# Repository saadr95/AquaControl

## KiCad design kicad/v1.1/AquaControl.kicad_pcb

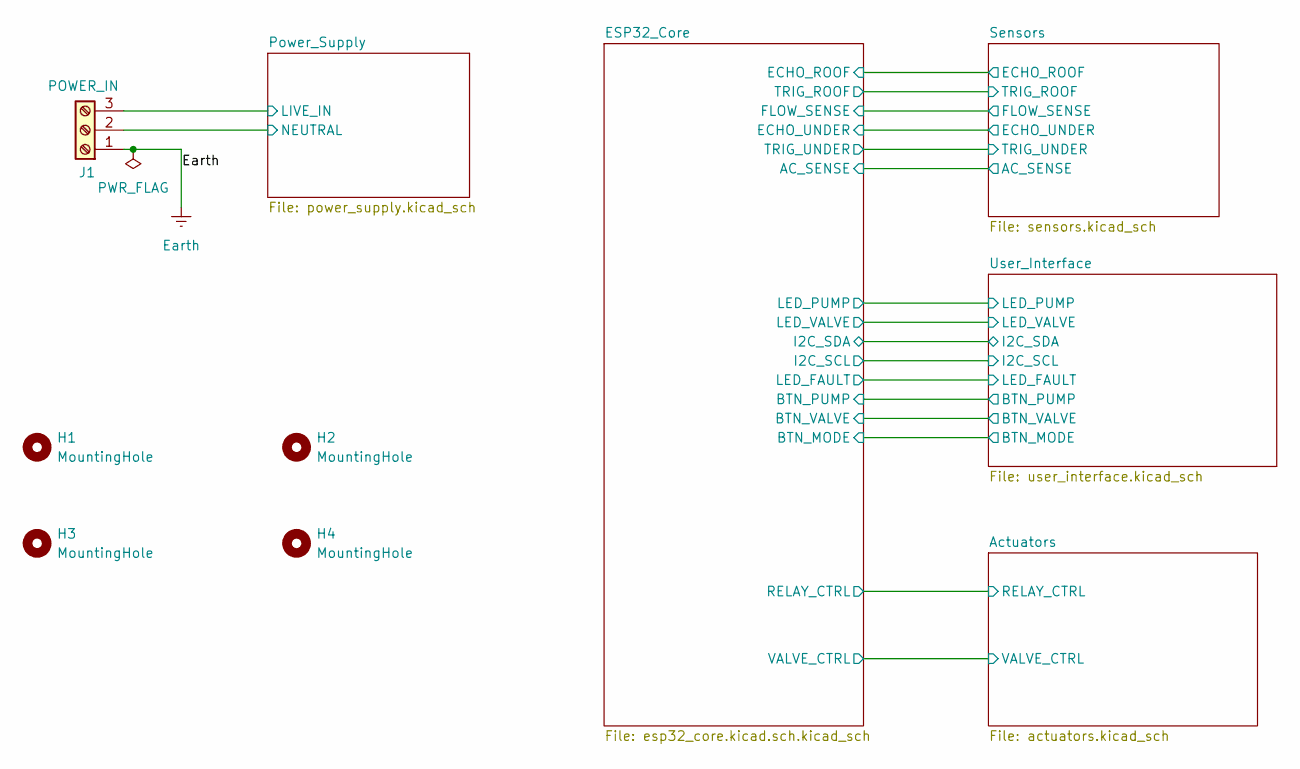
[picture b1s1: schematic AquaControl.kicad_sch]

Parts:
H1, H2, H3, H4: MountingHole; MountingHole_3.2mm_M3
J1: POWER_IN; TerminalBlock_Phoenix_MKDS-1,5-3_1x03_P5.00mm_Horizontal; LCSC C8427

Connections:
/Power_Supply/LIVE_IN: J1.3; also elsewhere on the board
/Power_Supply/NEUTRAL: J1.2; also elsewhere on the board
Earth: J1.1

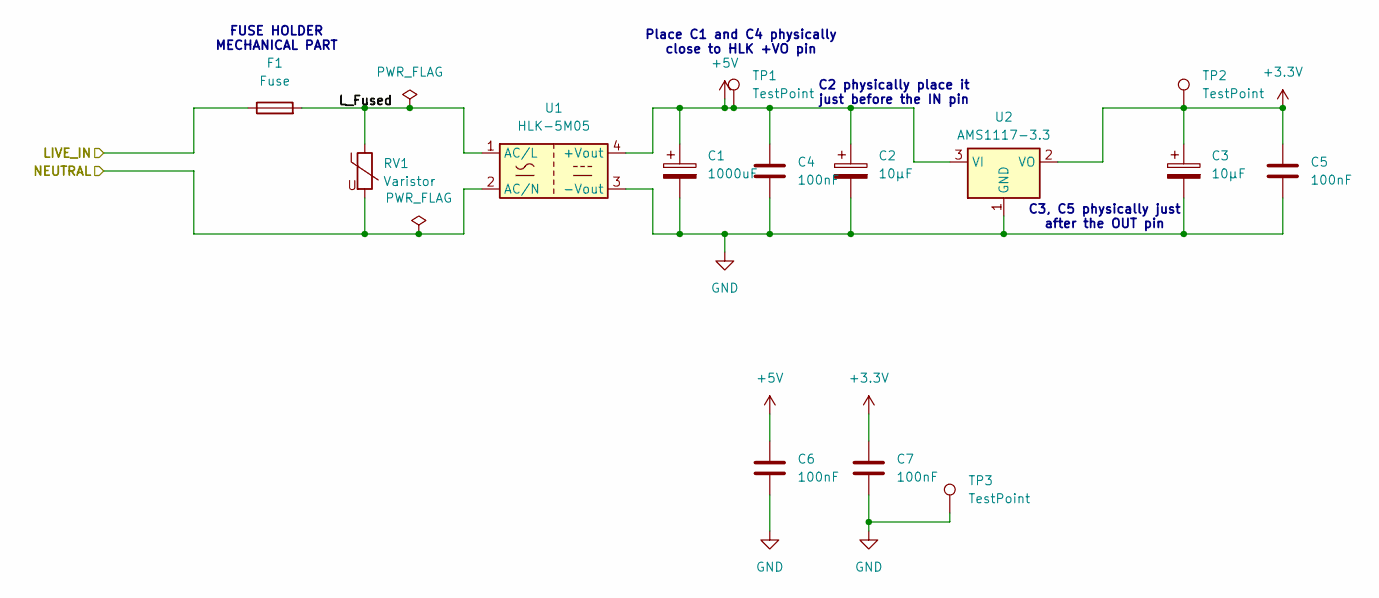
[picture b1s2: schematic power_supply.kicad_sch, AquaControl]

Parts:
C1: 1000uF; CP_Radial_D10.0mm_P5.00mm; LCSC C503217
C2, C3: 10µF; CP_Radial_D5.0mm_P2.50mm; LCSC C19712075
C4, C5, C6, C7: 100nF; C_0603_1608Metric; LCSC C14663
F1: Fuse; Fuseholder_Cylinder-5x20mm_Bulgin_FX0456_Vertical_Closed
RV1: Varistor; RV_Disc_D9mm_W3.3mm_P5mm; LCSC C125492
TP1, TP2, TP3: TestPoint; TestPoint_Pad_D1.0mm
U1: HLK-5M05; Converter_ACDC_Hi-Link_HLK-5Mxx; LCSC C48935095
U2: AMS1117-3.3; SOT-223-3_TabPin2; LCSC C6186

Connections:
+3.3V: C3.1, C5.1, C7.1, TP2.1 (1_1), U2.2 (VO); also elsewhere on the board
+5V: C1.1, C2.1, C4.1, C6.1, TP1.1 (1_1), U1.4 (+Vout), U2.3 (VI); also elsewhere on the board
/Power_Supply/LIVE_IN: F1.1; also elsewhere on the board
/Power_Supply/L_Fused: F1.2, RV1.1, U1.1 (AC/L)
/Power_Supply/NEUTRAL: RV1.2, U1.2 (AC/N); also elsewhere on the board
GND: C1.2, C2.2, C3.2, C4.2, C5.2, C6.2, C7.2, TP3.1 (1_1), U1.3 (-Vout), U2.1 (GND); also elsewhere on the board

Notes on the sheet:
C2 physically place it just before the IN pin
Place C1 and C4 physically close to HLK +VO pin
FUSE HOLDER MECHANICAL PART
C3, C5 physically just after the OUT pin

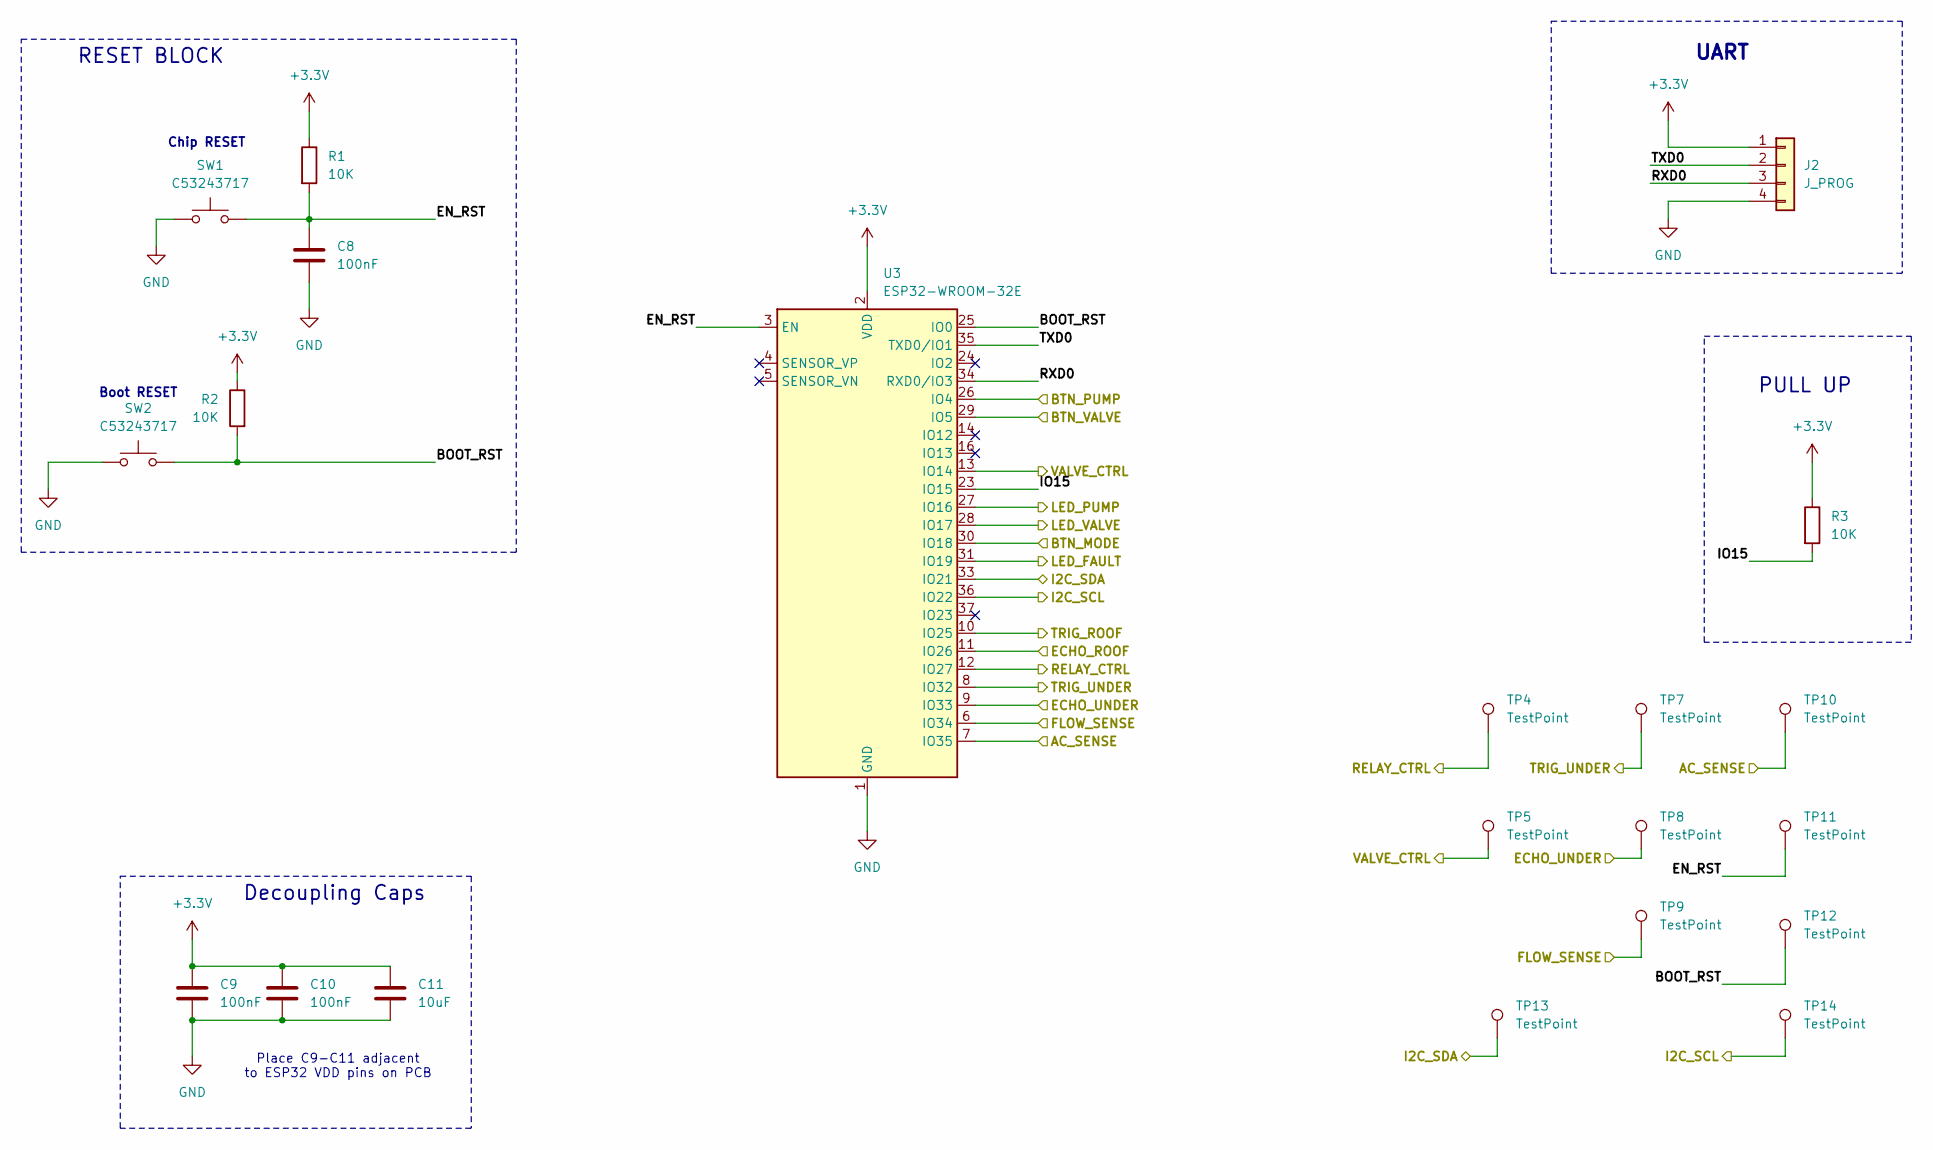
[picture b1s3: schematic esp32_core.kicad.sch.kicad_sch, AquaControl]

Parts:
C8, C9, C10: 100nF; C_0603_1608Metric; LCSC C14663
C11: 10uF; C_0603_1608Metric; LCSC C6119842
J2: J_PROG; PinHeader_1x04_P2.54mm_Vertical; LCSC C5116483
R1, R2, R3: 10K; R_0603_1608Metric; LCSC C2906982
SW1, SW2: C53243717; SW_PUSH_6mm_H4.3mm
TP4, TP5, TP7, TP8, TP9, TP10, TP11, TP12, TP13, TP14: TestPoint; TestPoint_Pad_D1.0mm
U3: ESP32-WROOM-32E; ESP32-WROOM-32D; LCSC C701341

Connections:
+3.3V: C9.1, C10.1, C11.1, J2.1, R1.1, R2.1, R3.1, U3.2 (VDD); also elsewhere on the board
/Actuators/RELAY_CTRL: TP4.1 (1_1), U3.12 (IO27); also elsewhere on the board
/Actuators/VALVE_CTRL: TP5.1 (1_1), U3.13 (IO14); also elsewhere on the board
/ESP32_Core/AC_SENSE: TP10.1 (1_1), U3.7 (IO35); also elsewhere on the board
/ESP32_Core/BOOT_RST: R2.2, SW2.1, TP12.1 (1_1), U3.25 (IO0)
/ESP32_Core/BTN_MODE: U3.30 (IO18); also elsewhere on the board
/ESP32_Core/BTN_PUMP: U3.26 (IO4); also elsewhere on the board
/ESP32_Core/BTN_VALVE: U3.29 (IO5); also elsewhere on the board
/ESP32_Core/ECHO_ROOF: U3.11 (IO26); also elsewhere on the board
/ESP32_Core/ECHO_UNDER: TP8.1 (1_1), U3.9 (IO33); also elsewhere on the board
/ESP32_Core/EN_RST: C8.1, R1.2, SW1.2, TP11.1 (1_1), U3.3 (EN)
/ESP32_Core/FLOW_SENSE: TP9.1 (1_1), U3.6 (IO34); also elsewhere on the board
/ESP32_Core/I2C_SCL: TP14.1 (1_1), U3.36 (IO22); also elsewhere on the board
/ESP32_Core/I2C_SDA: TP13.1 (1_1), U3.33 (IO21); also elsewhere on the board
/ESP32_Core/IO15: R3.2, U3.23 (IO15)
/ESP32_Core/LED_FAULT: U3.31 (IO19); also elsewhere on the board
/ESP32_Core/LED_PUMP: U3.27 (IO16); also elsewhere on the board
/ESP32_Core/LED_VALVE: U3.28 (IO17); also elsewhere on the board
/ESP32_Core/RXD0: J2.3, U3.34 (RXD0/IO3)
/ESP32_Core/TRIG_ROOF: U3.10 (IO25); also elsewhere on the board
/ESP32_Core/TRIG_UNDER: TP7.1 (1_1), U3.8 (IO32); also elsewhere on the board
/ESP32_Core/TXD0: J2.2, U3.35 (TXD0/IO1)
GND: C8.2, C9.2, C10.2, C11.2, J2.4, SW1.1, SW2.2, U3.1 (GND), U3.15 (GND), U3.38 (GND), U3.39 (GND); also elsewhere on the board

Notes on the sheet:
UART
PULL UP
Decoupling Caps
RESET BLOCK
Boot RESET
Place C9-C11 adjacent to ESP32 VDD pins on PCB
Chip RESET

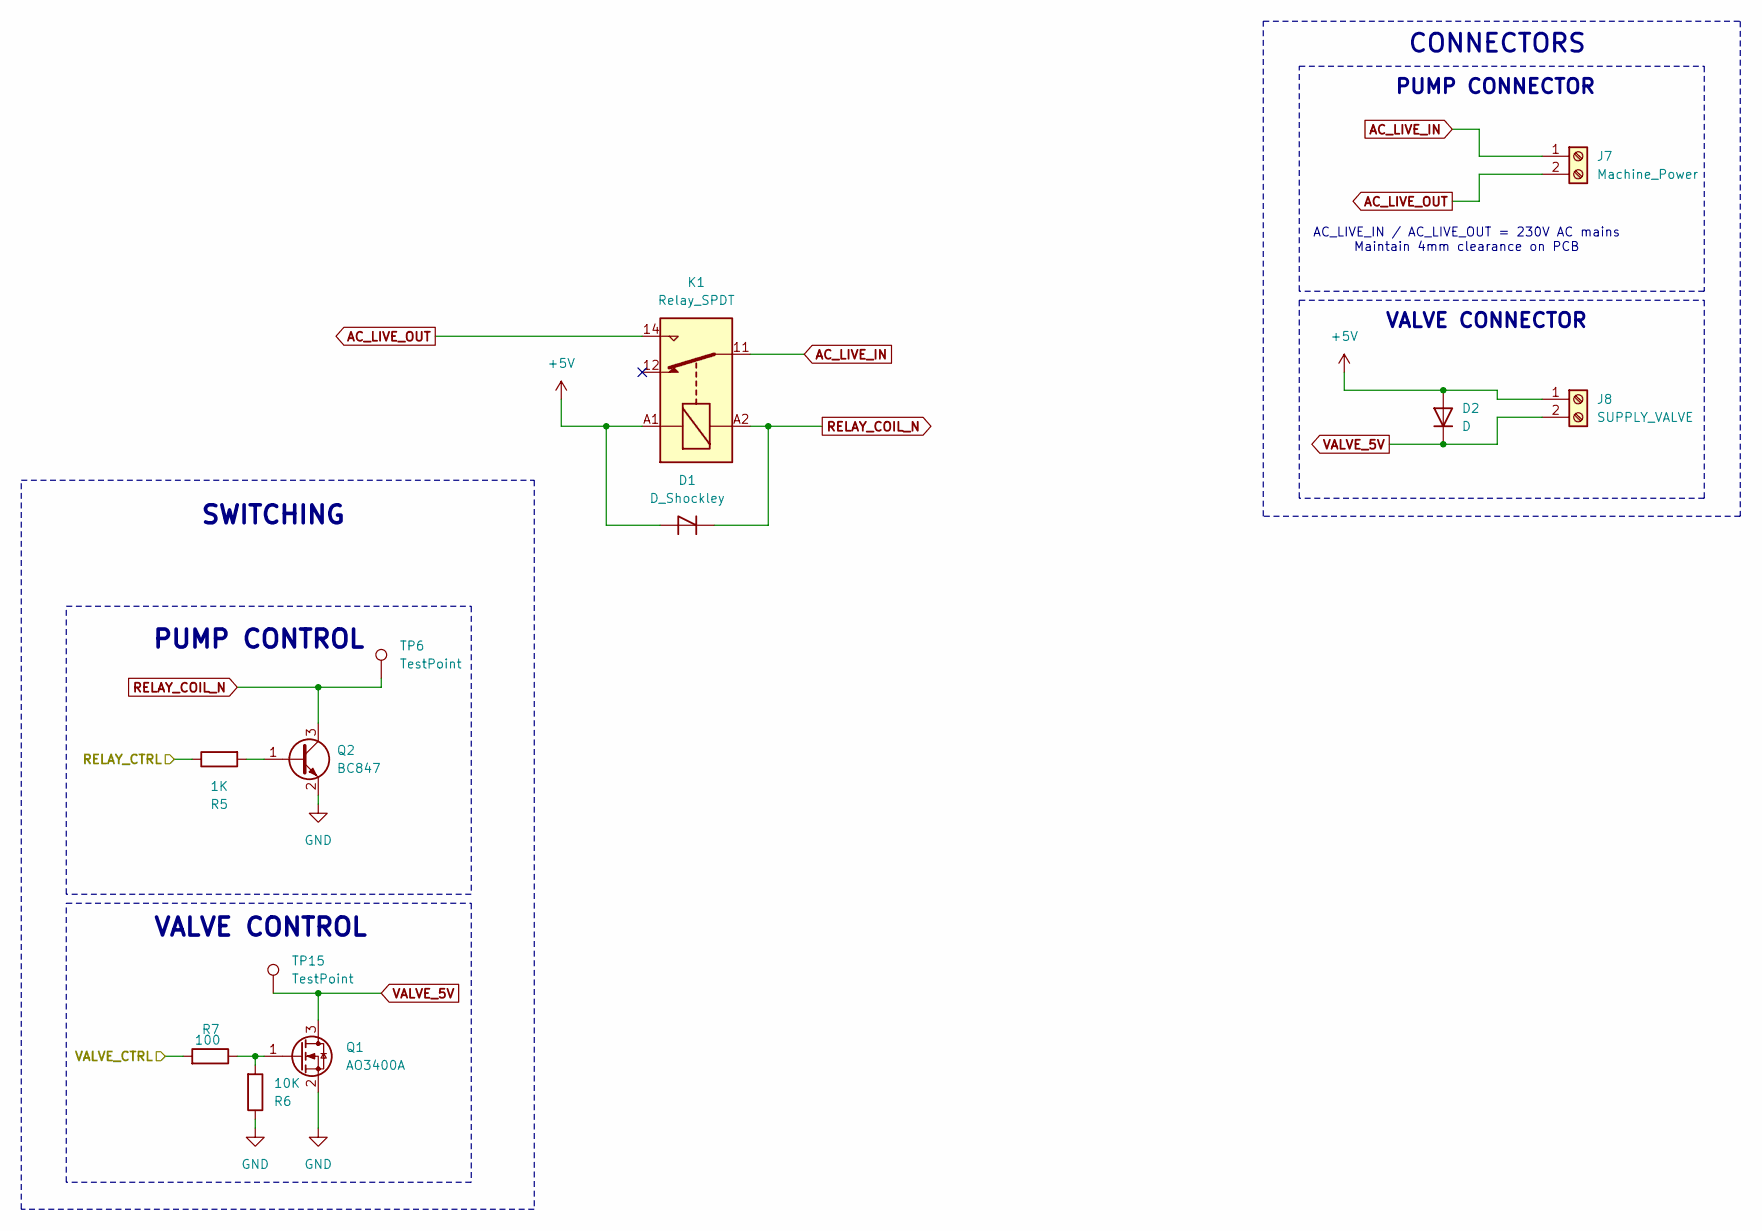
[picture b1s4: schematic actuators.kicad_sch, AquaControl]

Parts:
D1: D_Shockley; D_SMA; LCSC C2480
D2: D; D_SMA; LCSC C2480
J7: Machine_Power; TerminalBlock_Phoenix_MKDS-1,5-2_1x02_P5.00mm_Horizontal; LCSC C8439
J8: SUPPLY_VALVE; TerminalBlock_Phoenix_MKDS-1,5-2_1x02_P5.00mm_Horizontal; LCSC C8439
K1: Relay_SPDT; Relay_SPDT_Omron_G2RL-1; LCSC C1524672
Q1: AO3400A; SOT-23; LCSC C20917
Q2: BC847; SOT-23; LCSC C24698138
R5: 1K; R_0603_1608Metric; LCSC C2907002
R6: 10K; R_0603_1608Metric; LCSC C2906982
R7: 100; R_0603_1608Metric; LCSC C2906981
TP6, TP15: TestPoint; TestPoint_Pad_D1.0mm

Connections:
+5V: D1.2 (A), D2.2 (A), J8.1, K1.A1; also elsewhere on the board
/Actuators/RELAY_CTRL: R5.1; also elsewhere on the board
/Actuators/VALVE_CTRL: R7.2; also elsewhere on the board
AC_LIVE_IN: J7.1, K1.11
AC_LIVE_OUT: J7.2, K1.14
GND: Q1.2 (S), Q2.2 (E), R6.1; also elsewhere on the board
unnamed: Q1.1 (G), R6.2, R7.1
unnamed: Q2.1 (B), R5.2
RELAY_COIL_N: D1.1 (K), K1.A2, Q2.3 (C), TP6.1 (1_1)
VALVE_5V: D2.1 (K), J8.2, Q1.3 (D), TP15.1 (1_1)

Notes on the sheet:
VALVE CONTROL
VALVE CONNECTOR
CONNECTORS
PUMP CONTROL
SWITCHING
PUMP CONNECTOR
AC_LIVE_IN / AC_LIVE_OUT = 230V AC mains Maintain 4mm clearance on PCB

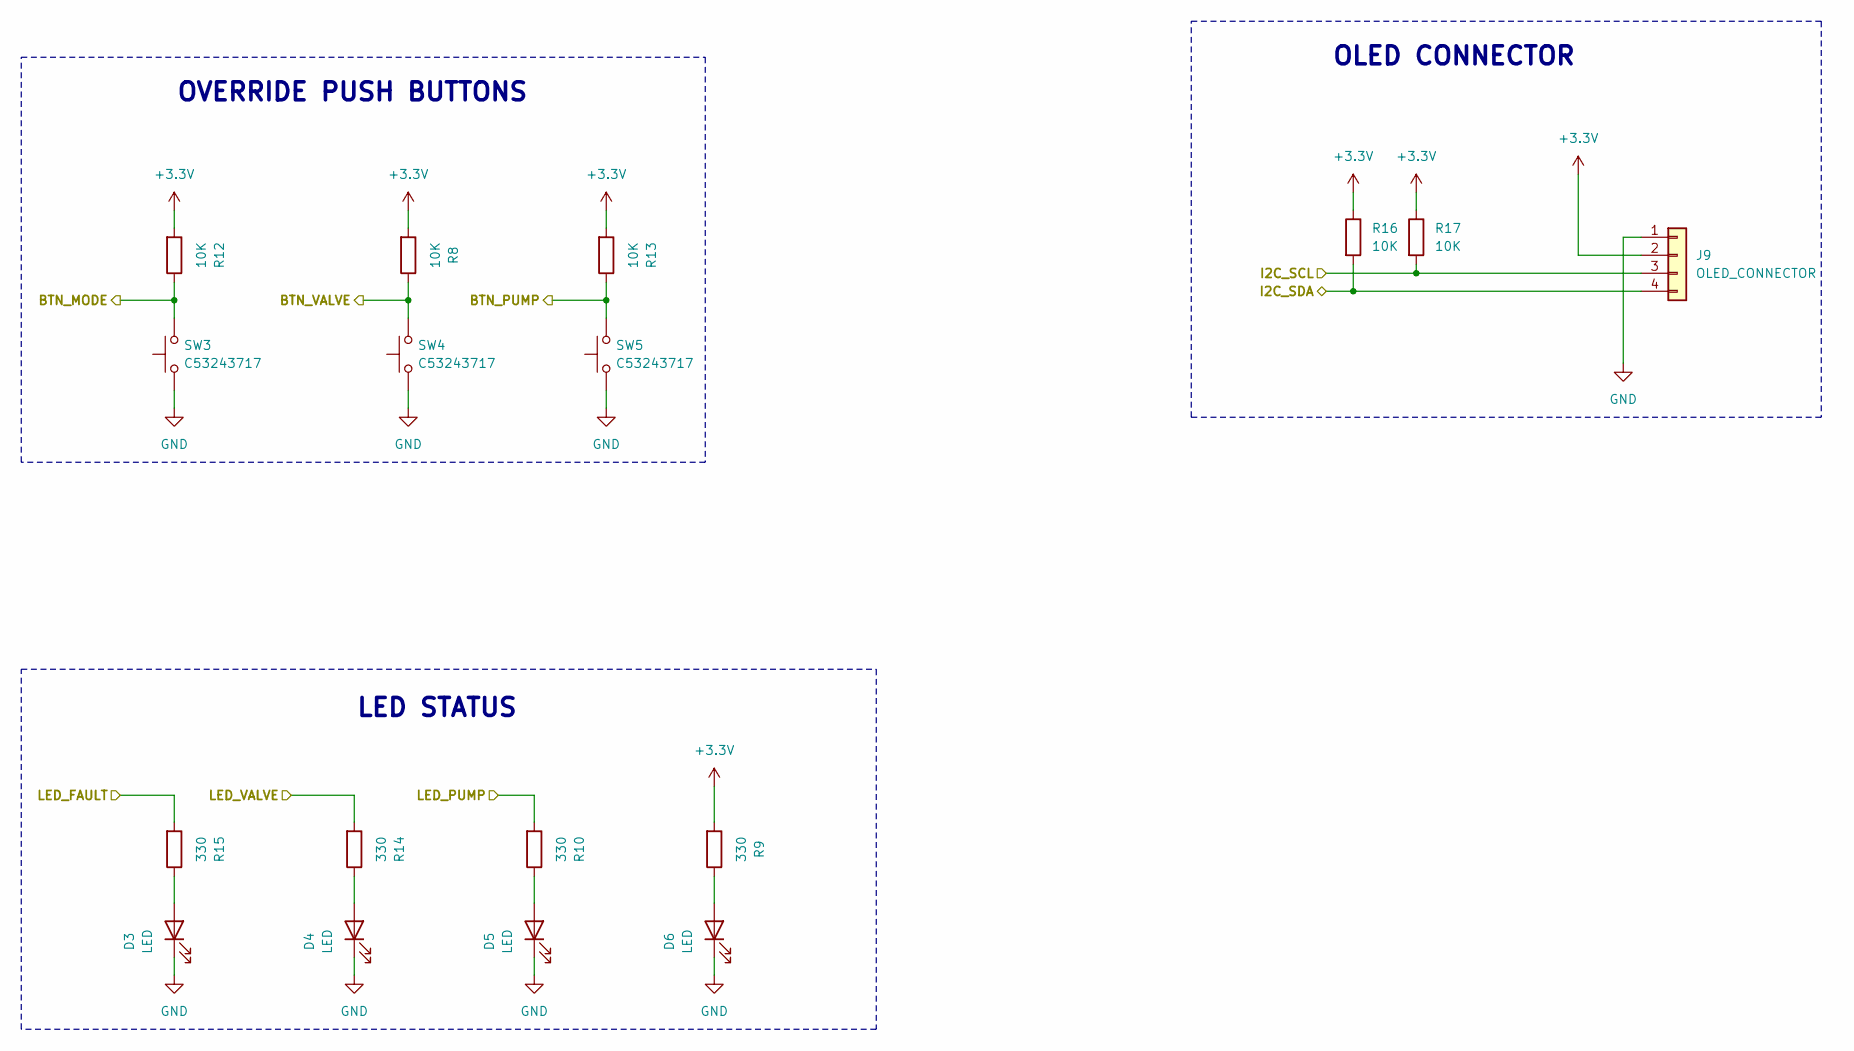
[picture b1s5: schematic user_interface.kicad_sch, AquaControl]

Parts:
D3, D4, D5, D6: LED; LED_0805_2012Metric; LCSC C84256
J9: OLED_CONNECTOR; Molex_PicoBlade_53047-0410_1x04_P1.25mm_Vertical; LCSC C5116483
R8, R12, R13, R16, R17: 10K; R_0603_1608Metric; LCSC C2906982
R9, R10, R14, R15: 330; R_0603_1608Metric; LCSC C701341
SW3, SW4, SW5: C53243717; SW_PUSH_6mm_H4.3mm

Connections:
+3.3V: J9.2, R8.2, R9.2, R12.2, R13.2, R16.1, R17.1; also elsewhere on the board
/ESP32_Core/BTN_MODE: R12.1, SW3.2; also elsewhere on the board
/ESP32_Core/BTN_PUMP: R13.1, SW5.2; also elsewhere on the board
/ESP32_Core/BTN_VALVE: R8.1, SW4.2; also elsewhere on the board
/ESP32_Core/I2C_SCL: J9.3, R17.2; also elsewhere on the board
/ESP32_Core/I2C_SDA: J9.4, R16.2; also elsewhere on the board
/ESP32_Core/LED_FAULT: R15.2; also elsewhere on the board
/ESP32_Core/LED_PUMP: R10.2; also elsewhere on the board
/ESP32_Core/LED_VALVE: R14.2; also elsewhere on the board
GND: D3.1 (K), D4.1 (K), D5.1 (K), D6.1 (K), J9.1, SW3.1, SW4.1, SW5.1; also elsewhere on the board
unnamed: D3.2 (A), R15.1
unnamed: D4.2 (A), R14.1
unnamed: D5.2 (A), R10.1
unnamed: D6.2 (A), R9.1

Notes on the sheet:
OLED CONNECTOR
OVERRIDE PUSH BUTTONS
LED STATUS

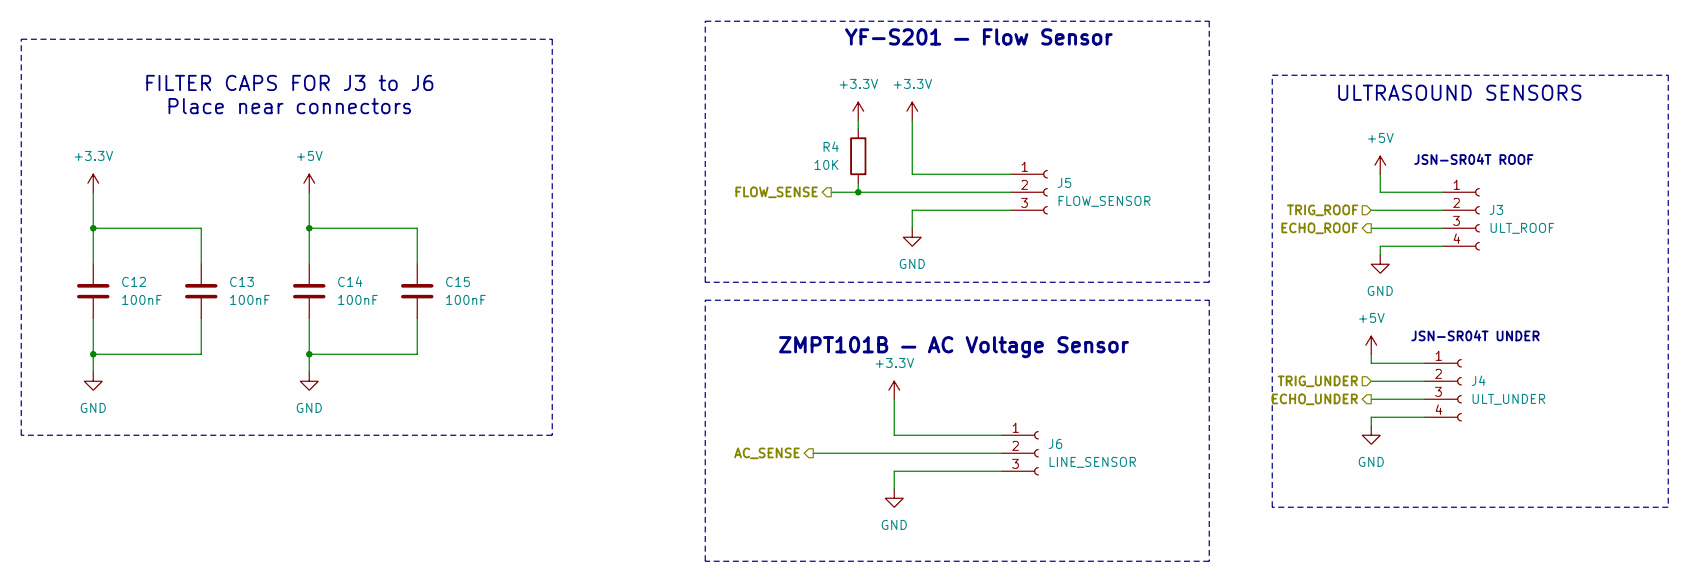
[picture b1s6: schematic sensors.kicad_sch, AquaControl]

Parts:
C12, C13, C14, C15: 100nF; C_0603_1608Metric; LCSC C14663
J3: ULT_ROOF; Molex_KK-254_AE-6410-04A_1x04_P2.54mm_Vertical; LCSC C5116483
J4: ULT_UNDER; Molex_KK-254_AE-6410-04A_1x04_P2.54mm_Vertical; LCSC C5116483
J5: FLOW_SENSOR; Molex_KK-254_AE-6410-03A_1x03_P2.54mm_Vertical; LCSC C429954
J6: LINE_SENSOR; Molex_KK-254_AE-6410-03A_1x03_P2.54mm_Vertical; LCSC C429954
R4: 10K; R_0603_1608Metric; LCSC C2906982

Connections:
+3.3V: C12.1, C13.1, J5.1, J6.1, R4.1; also elsewhere on the board
+5V: C14.1, C15.1, J3.1, J4.1; also elsewhere on the board
/ESP32_Core/AC_SENSE: J6.2; also elsewhere on the board
/ESP32_Core/ECHO_ROOF: J3.3; also elsewhere on the board
/ESP32_Core/ECHO_UNDER: J4.3; also elsewhere on the board
/ESP32_Core/FLOW_SENSE: J5.2, R4.2; also elsewhere on the board
/ESP32_Core/TRIG_ROOF: J3.2; also elsewhere on the board
/ESP32_Core/TRIG_UNDER: J4.2; also elsewhere on the board
GND: C12.2, C13.2, C14.2, C15.2, J3.4, J4.4, J5.3, J6.3; also elsewhere on the board

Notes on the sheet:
JSN-SR04T ROOF
FILTER CAPS FOR J3 to J6 Place near connectors
ZMPT101B — AC Voltage Sensor
ULTRASOUND SENSORS
JSN-SR04T UNDER
YF-S201 — Flow Sensor

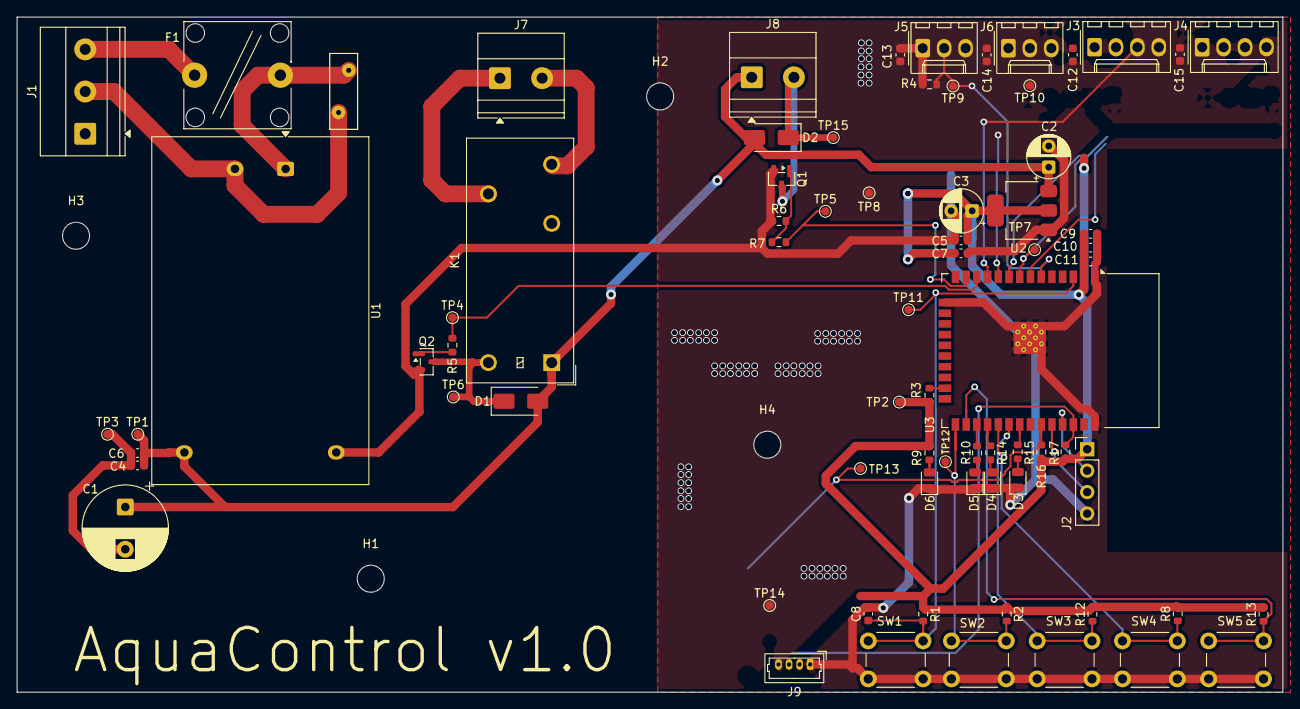
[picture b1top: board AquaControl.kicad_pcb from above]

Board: 2 copper layers, 150.0 x 80.0 mm, 78 parts (0 on the bottom side), 37 nets.

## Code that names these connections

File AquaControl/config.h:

#pragma once

// ═══════════════════════════════════════════════════════════
// AquaControl v1.0 — Configuration
// ESP32-WROOM-32E
// ═══════════════════════════════════════════════════════════

// ── Firmware version / OTA ─────────────────────────────────────
// Bump FW_VERSION with every release you publish to GitHub — it's what
// shows up in the app and in Serial. GitHub's "latest" release alias
// always resolves to whatever was most recently published under that
// exact asset name, so the URL below never needs to change.
#define FW_VERSION   "1.1.6"
#define OTA_URL      "https://github.com/saadr95/AquaControl/releases/latest/download/firmware.bin"

// ── WiFi ────────────────────────────────────────────────────
// No hardcoded SSID/password — see wifi_setup.h. On first boot (or after
// a WiFi reset) the board opens its own setup hotspot; connect a phone to
// it to enter the real network's credentials. Saved to flash from then on.
#define WIFI_SETUP_AP_PREFIX   "AquaControl-Setup"   // + short device ID
#define WIFI_SETUP_AP_PASSWORD "aquasetup123"        // portal hotspot password
#define WIFI_PORTAL_TIMEOUT_S  180                    // give up & retry later

// ── MQTT ────────────────────────────────────────────────────
// HiveMQ public broker — unauthenticated, anyone can publish to the
// commands topic. Fine for bench testing; swap for a private/authenticated
// broker before this runs unattended, since commands drive the pump relay.
//
// Client ID and topics are built at runtime from each board's unique
// hardware ID (see identity.h) — aquacontrol/<device_id>/status etc. —
// so multiple boards can share this broker without colliding.
#define MQTT_BROKER                 "broker.hivemq.com"
#define MQTT_PORT                   1883
#define MQTT_CLIENT_ID_PREFIX       "aquacontrol_"
#define MQTT_TOPIC_PREFIX           "aquacontrol/"
#define MQTT_PUBLISH_INTERVAL_MS    5000    // status publish rate
#define MQTT_RECONNECT_INTERVAL_MS  5000    // min gap between reconnect attempts

// ── Sensor Pins ─────────────────────────────────────────────
#define TRIG_UNDER        32
#define ECHO_UNDER        33
#define TRIG_ROOF         25
#define ECHO_ROOF         26
#define FLOW_SENSE        34
#define AC_SENSE          35

// ── Actuator Pins ───────────────────────────────────────────
#define RELAY_CTRL        27    // pump — HIGH = ON
#define VALVE_CTRL        14    // solenoid valve — HIGH = OPEN

// ── UI Pins ─────────────────────────────────────────────────
#define BTN_PUMP          4     // active LOW
#define BTN_VALVE         5     // active LOW
#define BTN_MODE          18    // active LOW
#define LED_PUMP          16    // HIGH = ON
#define LED_VALVE         17    // HIGH = ON
#define LED_FAULT         19    // HIGH = ON

// ── I2C ─────────────────────────────────────────────────────
#define OLED_SDA          21
#define OLED_SCL          22
#define OLED_ADDRESS      0x3C
#define OLED_WIDTH        128
#define OLED_HEIGHT       64

// ── Tank Configuration ───────────────────────────────────────
// JSN-SR04T mounted at top of tank, measuring distance to water
// Distance = empty, small distance = full

#define UNDER_TANK_DEPTH_CM     180   // full depth of underground tank in cm
#define ROOF_TANK_DEPTH_CM      120   // full depth of roof tank in cm

#define UNDER_TANK_LOW_PCT      20    // % — start filling underground
#define UNDER_TANK_HIGH_PCT     95    // % — stop filling underground
#define UNDER_TANK_MIN_PCT      15    // % — too low to run pump safely
#define UNDER_TANK_RESUME_PCT   50    // % — buffer reached while refilling:
                                      //     start the pump to roof now, with
                                      //     supply still topping underground.
                                      //     Must sit comfortably above MIN so
                                      //     the pump won't drain back to MIN.

#define ROOF_TANK_LOW_PCT       25    // % — start filling roof
#define ROOF_TANK_HIGH_PCT      95    // % — stop filling roof

// ── Timing ──────────────────────────────────────────────────
#define SENSOR_READ_INTERVAL_MS     5000    // read sensors every 5s
#define FLOW_CHECK_DURATION_MS      5000    // how long to check for flow
#define DEBOUNCE_MS                 50      // button debounce time
#define PERMISSION_TIMEOUT_MS       300000  // 5 min — auto-deny if no response
#define SUPPLY_RETRY_MS             600000  // 10 min — wait before re-checking supply
#define BTN_RELEASE_TIMEOUT_MS      1500    // max wait for button release (anti-hang)

// ── Fault tolerance ─────────────────────────────────────────
#define MAX_SENSOR_ERRORS           5       // consecutive bad reads before FAULT

// ── AC Sense ────────────────────────────────────────────────
#define AC_SENSE_THRESHOLD    50   // ADC value above this = grid present
                                    // tune after hardware testing
#define GRID_DEBOUNCE_READS   3    // consecutive consistent reads (~15s at
                                    // SENSOR_READ_INTERVAL_MS) before a grid
                                    // state change is accepted as real

// ── Ultrasonic ──────────────────────────────────────────────
#define MAX_DISTANCE_CM       300   // max range for JSN-SR04T
#define SENSOR_READINGS       9     // ping attempts per read (median of valid)

// ── Flow Rate (YF-S201) ───────────────────────────────────────
#define FLOW_PULSES_PER_LITRE  450.0  // sensor calibration constant (datasheet)
#define FLOW_RATE_SAMPLE_MS    1000   // how often the live rate is recalculated
#define MIN_FLOW_LPM           0.2    // above this, "flow" reads as detected

// ── System Modes ────────────────────────────────────────────
#define MODE_AUTO             0
#define MODE_MANUAL           1
